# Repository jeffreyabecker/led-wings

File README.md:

# Wings

One-off LED-lit wing costume — off-the-shelf SK9822 strips cut into per-feather chunks, data
daisy-chained chunk-to-chunk, power fed from buck-module power-hubs, driven by a Pixelblaze.

## Build strategy

- **Off-the-shelf electrical system** — no custom PCBs for this build. SK9822 96 LED/m strips
  cut to per-feather LED counts; Pixelblaze V3 controller; buck-module + fuse power-hubs.
- Custom boards (KiCad 10 + `pcbnew` parameterized feathers) are deferred to "if we build
  more than one".

## Boards

- [Boards](boards/README.md) — the build plan: strip-chunk cut table, covert rows, controller,
  power hubs, settled COTS parts. **Source of truth for the electrical build.**

## Feather templates

- [Templates](mechanical/templates/) — **physical feather templating only**: outlines + geometry,
  the generator, and shape sourcing. No electronics content — lighting lives in
  [boards/lighting-and-boards.md](boards/lighting-and-boards.md).

## Mechanical

- [Mechanical](mechanical/) — physical wing structure: [structural](mechanical/structural/) frame

## Shared docs

- [Connector pinout](docs/connector-pinout.md) — pigtail wiring legend (PWR / DATA-IN / DATA-OUT wire pairs + colors)

## Investigations

- [Battery](investigations/battery/) — 12 V chemistry + sizing for 8 h @ 20 % mobility
- [Connectors](investigations/connectors/) — board-to-wire family options for the strip ends
  (pitch-split power/data, JLCPCB-assembled)

## Repository layout

- `boards/` — **electrical build**: strategy, feather lighting map, wiring legend, settled
  parts. All electronics information lives here (or in `docs/`).
- `mechanical/templates/` — **physical feather templating only**: outlines, geometry, generator,
  shape sourcing. No electronics/lighting content — that belongs in `boards/`.
- `mechanical/` — wing structure (frame, backplate, harness mounts).
- `docs/` — shared electrical references (connector pinout, pigtail crimp guide).
- `investigations/` — one-off research (battery, connectors, diffuser halo).

## Changing the plan

Update [boards/README.md](boards/README.md) — it is the single source of truth for the
electrical build.

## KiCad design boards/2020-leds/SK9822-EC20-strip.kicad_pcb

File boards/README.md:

# Boards — Off-the-Shelf Build Plan (one-off)

> ⚠️ **Board subset (2026-08, updated):** this build now makes **8 custom group boards/wing**
> (P, S, A, PC, SC, MC, L, U — [feather-boards.md](feather-boards.md)) + **4 × 6 A hub
> boards/wing** ([hub-board.md](hub-board.md)). The off-the-shelf strip-chunk plan below is
> **superseded for the boards** (retained as the parts/wiring reference and fallback).
>
> **Strategy (settled ✅):** this is a **one-off build** — the electrical system is assembled
> from off-the-shelf SK9822 strips and modules. **No custom PCBs for this build**; the
> parameterized custom-board plan (KiCad + `pcbnew`) and the 6-pin hub-routed idea are
> **deferred** to "if we ever build more than one".
>
> Status: ✅ settled · ⚠️ to confirm · ⬜ TBD.

| Role | Status | Implementation |
|------|--------|----------------|
| Feather lighting | ✅ | SK9822 strip chunks (96 LED/m), one cut per lit feather |
| Covert strip rows | ✅ | Continuous SK9822 strip spans, one cut per row |
| Controller | ✅ | Pixelblaze V3 + 74AHCT125 level shifter (COTS modules) |
| Power hub | ✅ | Buck modules + fuse blocks on perfboard |

## System (locked)

- **Split power/data.** Data daisy-chains feather→feather (pigtails) from one central
  Pixelblaze driving **both wings**; power fans out from hub clusters on a 12 V bus. 5 V
  exists only on the short hub→feather runs.
- **Controller:** Pixelblaze V3 Standard (ElectroMage) — ESP32, 8 data channels, 3.3 V logic.
  **Segmentation (settled ✅): N = 2 chains — one per wing** (all feathers + covert rows of
  that wing). No Output Expander.
- **Pixels:** ~1270 LEDs total both wings (see
  [feather lighting](lighting-and-boards.md)). Chain budget ≈ 635
  LEDs/channel on 2 channels — a full frame at 8 MHz SPI ≈ 2.5 ms, well inside any pattern
  frame rate.
- **Routing:** the two chains (one per wing) run along the wing's **top edge** (the feather
  bases — the only cable entrance); hubs sit along the same edge feeding short 5 V runs into
  clusters.

## LED medium — SK9822 strip

- **Strip (96/m only, settled ✅):** SK9822 **96 LED/m** (≈10.4 mm pitch), **10 mm wide**,
  5050 — the near-exact match to the 10 mm-pitch map. ⚠️ Vendor shortlist (96/m only):
  [Alibaba multi-density listing](https://www.alibaba.com/product-detail/Individually-Addressable-APA102-SK9822-30-60_1601370513576.html)
  (96/m option) or [JAD-LEDS 96/m](https://jad-leds.com/dc5v-ic-external-led-strip/467.html) —
  see settled parts; validate one reel before ordering the rest.
- **Feather = cut chunk.** One chunk per lit feather, cut per-LED (every LED carries its own
  chip). LED count = exposed-tip map + 2-LED bleed, at 10.4 mm pitch — same counts as the
  10 mm-pitch map:

  > ⚠️ Chunk lengths/LED counts below derive from **provisional** feather sizing — the
  > authoritative sizing lives in [`mechanical/templates/`](../mechanical/templates/),
  > **not yet finalized**; re-cut counts once it is locked.

  | Group | Exposed (cm) | Bleed | Chunk LEDs | Chunk length |
  |-------|-------------:|------:|-----------:|-------------:|
  | Primaries P1–P10 | 15 | +2 | 17 | ~17.7 cm |
  | Secondaries S1–S12 | 12 | +2 | 14 | ~14.6 cm |
  | Tertials T1–T4 | 10 | +2 | 12 | ~12.5 cm |
  | Greater coverts GC1–GC12 | 8 | +2 | 10 | ~10.4 cm |
  | Alula A-B/A-T | ~8 ⚠️ | +2 | ~10 ⚠️ | ~10.4 cm |

- **Chunk termination (settled ✅):** 6 stub wires soldered per chunk — `+5V`/`GND` (power,
  from a hub), `DI`/`CI` (data in), `DO`/`CO` (data out to the next feather) — then
  **2-pin JST-PNI crimped pigtails** (2.0 mm, wire-to-wire — both ends crimped, no headers):
  a receptacle `PNIRR-02VF` on each of power-in / data-in / data-out; all jumpers and feeds
  are plugs `PNIRP-02V-S` (data jumpers plug–plug, hub/controller feeds plug + bare wire).
  Wire pairs + colors are the [wiring legend](../docs/connector-pinout.md); parts + crimp
  procedure in [pigtail crimping](../docs/pigtail-crimping.md). Epoxy/glue strain relief over
  every pad set; bench-test each chunk before mounting (a bad joint darkens the whole
  downstream chain).
- **Covered base:** no strip at all — only the exposed tip + bleed is lit, so there are no
  hidden LEDs (and no idle-current waste).
- **Limits:** a 17-LED chunk ≈ 0.68 A full white — strip copper handles it easily; wiring
  planned so no single run exceeds ~2–3 A (PNI class rating).

## Covert strip rows

- One **continuous strip span per row** (median / lesser / marginal) — no cuts except row
  length, one common LED orientation by construction. The scallop silhouette lives in the
  overlay/diffuser, **not** in the strip.
- **Wiring per row:** `PWR` + `DI`/`CI` at the row head; `DO`/`CO` at the tail → next row's
  head (or its own chain).
- **Rows (working ⚠️):** median ~28 cm (~27 LEDs), lesser ×2 ~28 cm, marginal ~28 cm.
  Full-white per row ≈ 1.1 A — feed at the row head; mid-span power injection only if the
  bench shows drop.

## Controller — Pixelblaze (COTS)

- **Pixelblaze V3 Standard** (ElectroMage) — ✅ settled. 8 channels, 3.3 V logic, web UI
  live-coding (patterns ride for free). **N = 2 chains (settled ✅) — one per wing; no
  Output Expander.**
- **Level shifting:** the Pixelblaze's 3.3 V outputs need 5 V logic per chain — a
  74AHCT125-class shifter module (2 of 4 gates used) at the controller.
- Series R (33–100 Ω) at each chain head only if bench testing shows ringing; ESD/TVS
  optional for a one-off.

## Power hubs — modules, not boards

- **Buck:** **MP1584EN** module per cluster — rated 3 A, **practical ~2–2.5 A** at 12→5 V
  (**no heatsink needed**; ⚠️ buy from a reputable vendor — counterfeits common; bench-test
  each before install). One hub serves a feather cluster: ~0.4 A/feather full white,
  ~0.08 A @ 20 %. **Cluster sizing rule:** keep each hub ≤ ~2 A full-white (≈5 feathers), so
  it stays inside the no-heatsink envelope.
- **Protection:** fuse per 5 V feed (ATO inline holder or polyfuse), reverse-polarity MDD
  `SS34` ([C8678](https://www.lcsc.com/product-detail/C8678.html)) on the 12 V input.
- **Form:** perfboard — buck module + fuses + **push-in (spring-clamp) terminals**
  (Wago 2060-class) on the perfboard — **no screw terminals** (vibration-proof, tool-less,
  lower profile). **No data** on the hub.
- **Hub wiring:** 12 V bus → (fused + `SS34`) → push-in terminal → MP1584EN `IN+/IN−`;
  `OUT+/OUT−` → push-in 5 V terminals → PNI plug feeds to the chunks.
- **12 V bus:** daisy-chain hub-to-hub with **Wago 221 lever nuts** (tool-less splices,
  vibration-proof); drop-tolerant.
- **Why 12 V (settled):** a 5 V bus can't scale — on a 2 m / 12 AWG reference bus, full-white
  drops ~33 % (color shift; blue dies first) vs ~6 % on 12 V (~1 % @ 20 % brightness). One
  MP1584EN covers a hub's cluster at ≤ ~2 A full-white (~0.4 A @ 20 %) — inside its
  no-heatsink envelope.

## Settled parts (COTS)

| Item | Choice | Qty | Status | Source |
|------|--------|-----|--------|--------|
| LED strip | SK9822 96 LED/m, 10 mm wide, 5050 | ~15 m (3×5 m reels) | ⚠️ | [Alibaba 30/60/96/144 listing](https://www.alibaba.com/product-detail/Individually-Addressable-APA102-SK9822-30-60_1601370513576.html) · [JAD-LEDS 96/m](https://jad-leds.com/dc5v-ic-external-led-strip/467.html) |
| Controller | Pixelblaze V3 Standard | 1 | ✅ | [Tindie](https://www.tindie.com/products/electromage/pixelblaze-v3-standard-wifi-led-controller/) |
| Level shifter | Adafruit 74AHCT125 Quad Level-Shifter breakout (2 of 4 gates) | 1 | ✅ | [Adafruit 1787](https://www.adafruit.com/product/1787) |
| Buck | MP1584EN module (3 A; practical ~2–2.5 A, no heatsink) — cluster ≤ ~2 A full-white | ~6–8 | ⚠️ | [Amazon MP1584EN 5-pk](https://www.amazon.co.uk/DollaTek-MP1584EN-Step-Down-Adjustable-Converter/dp/B07DJ5HZ7G) — test each (counterfeits common) |
| Fuse | ATO inline holder per 5 V feed (alt. polyfuse e.g. Littelfuse 30R) | ~10 | ⚠️ | [Youngneer ATO kit](https://www.amazon.sg/Youngneer-Holders-Standard-Harness-Waterproof/dp/B07YY6KWSY) |
| Reverse polarity | MDD `SS34`, 3A 40V SMA | 1/hub | ✅ | [LCSC C8678](https://www.lcsc.com/product-detail/C8678.html) |
| PNI receptacle (chunk ends) | JST `PNIRR-02VF`, 2-pin | ~300 | ⬜ | TBD |
| PNI plug (jumpers/feeds) | JST `PNIRP-02V-S`, 2-pin | ~300 | ⬜ | TBD |
| PNI contacts | Socket `SPNI-001T-P0.5` + pin `BPNI-001T-P0.5` | ~650 + ~650 | ⬜ | TBD |
| Crimp tool | JST PN-family tool / ratchet + PN dies (SN-28B does NOT fit) | 1 | ⬜ | TBD |
| Wire | Silicone — 20–22 AWG red/black (power), 24 AWG data colors | ~15 m each | ⬜ | TBD |

## Open decisions (compact)

- Strip vendor: pick between the [Alibaba multi-density listing](https://www.alibaba.com/product-detail/Individually-Addressable-APA102-SK9822-30-60_1601370513576.html)
  and [JAD-LEDS](https://jad-leds.com/dc5v-ic-external-led-strip/467.html); confirm 10 mm
  width + open (non-waterproof) PCB, validate one reel before bulk
- Diffuser gap validation on 5050 emitters (prototype with the first reel)
- Buck module brand + bench test; fuse rating per feed
- Alula chunk size (confirm mockup); covert row spans once the layout is drawn

## Deferred (if we ever build more than one)

- Custom feather boards — 2020 SK9822 (`SK9822-EC20`, C2909059), JST connectors,
  parameterized KiCad 10 + `pcbnew` geometry (10 mm width, length + bend points).
- Custom power-hub PCB and controller carrier.
- Shelved idea: single 6-pin power+data connector per feather with hub-routed data chaining.

## References

- [Connector pinout / wiring legend](../docs/connector-pinout.md) — PWR / DATA-IN / DATA-OUT wire pairs + colors
- [Pigtail crimping](../docs/pigtail-crimping.md) — JST-PNI parts, counts, crimp procedure
- [Parts list](parts-list.md) — summarized COTS parts + potential vendors (battery excluded)
- [Battery](../investigations/battery/) — 12 V source sizing
- [Feather lighting](lighting-and-boards.md) — LED map + chunk counts
- [SK9822 datasheet (Normand LED)](http://www.normandled.com/upload/202003/SK9822-EC20%20LED%20Datasheet.pdf)

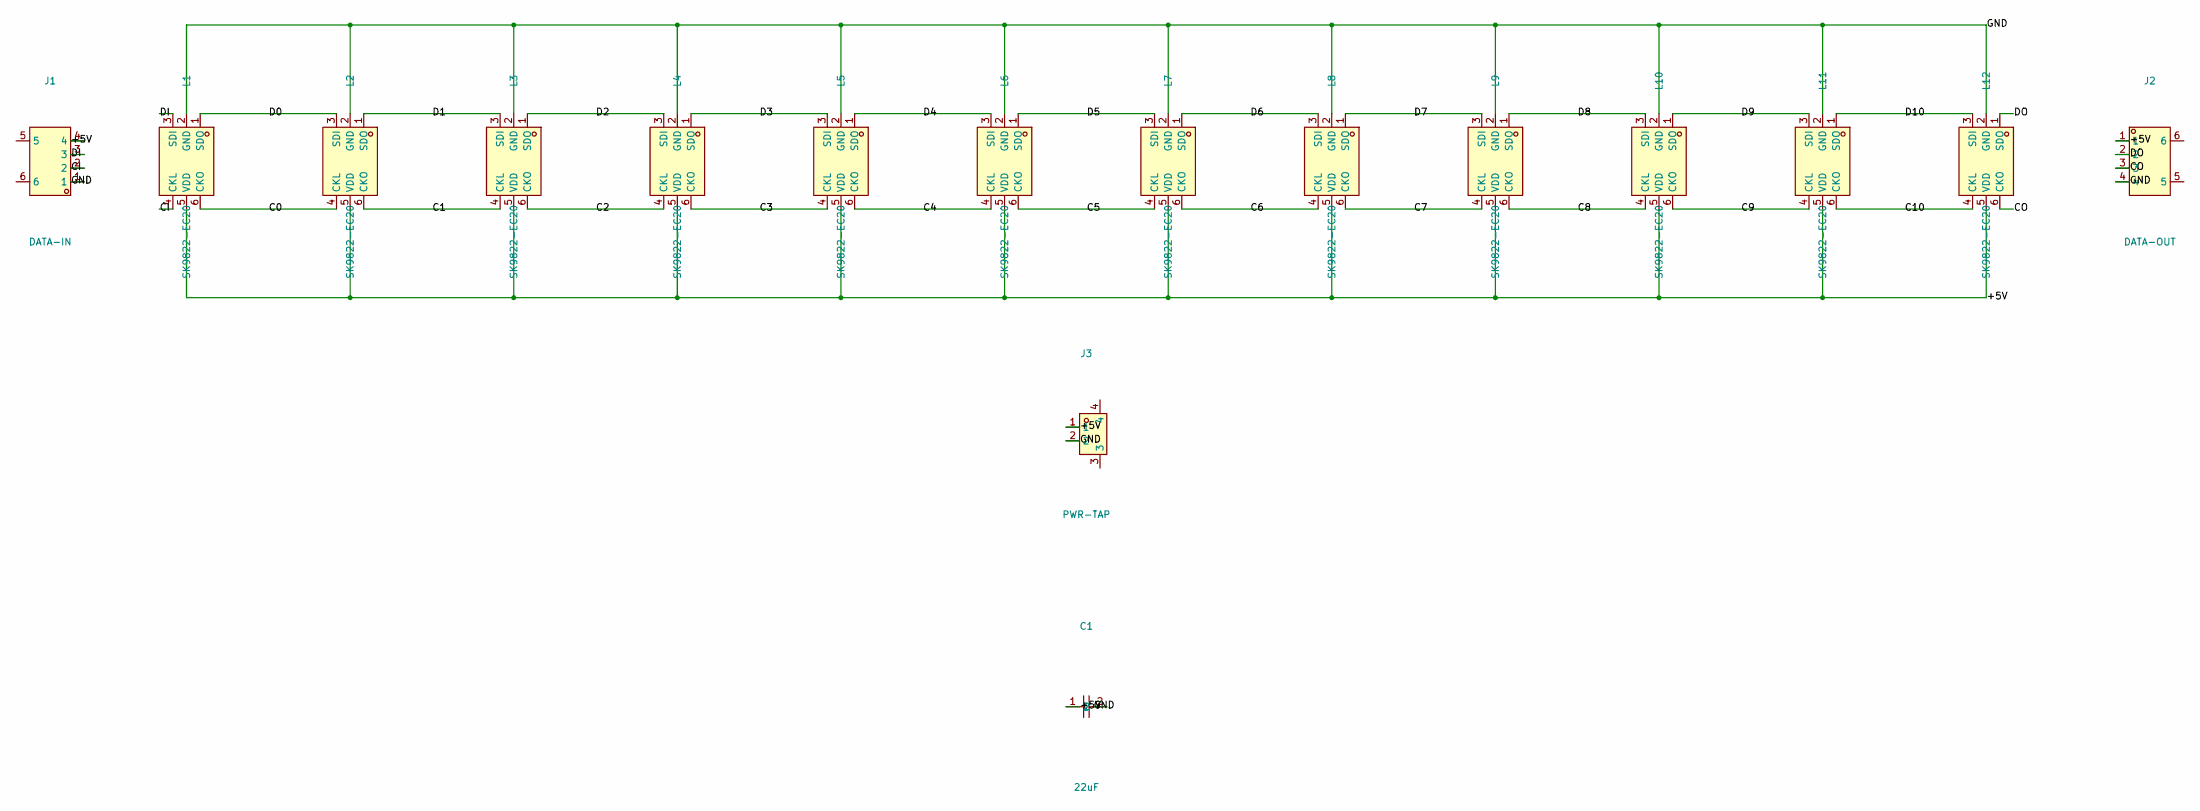
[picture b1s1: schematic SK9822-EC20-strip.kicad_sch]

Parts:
C1: 22uF; C1206
J1: DATA-IN; CONN-SMD_ZH1.5-4P_SMD
J2: DATA-OUT; CONN-SMD_ZH1.5-4P_SMD
J3: PWR-TAP; CONN-SMD_2P-P2.00_PH2.0-SPWB
L1, L2, L3, L4, L5, L6, L7, L8, L9, L10, L11, L12: SK9822-EC20; LED-SMD_6P-L2.0-W2.0-P0.80-TL

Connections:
/+5V: C1.1, J1.4, J2.1, J3.1, L1.5 (VDD), L2.5 (VDD), L3.5 (VDD), L4.5 (VDD), L5.5 (VDD), L6.5 (VDD), L7.5 (VDD), L8.5 (VDD), L9.5 (VDD), L10.5 (VDD), L11.5 (VDD), L12.5 (VDD)
/C0: L1.6 (CKO), L2.4 (CKL)
/C1: L2.6 (CKO), L3.4 (CKL)
/C2: L3.6 (CKO), L4.4 (CKL)
/C3: L4.6 (CKO), L5.4 (CKL)
/C4: L5.6 (CKO), L6.4 (CKL)
/C5: L6.6 (CKO), L7.4 (CKL)
/C6: L7.6 (CKO), L8.4 (CKL)
/C7: L8.6 (CKO), L9.4 (CKL)
/C8: L9.6 (CKO), L10.4 (CKL)
/C9: L10.6 (CKO), L11.4 (CKL)
/C10: L11.6 (CKO), L12.4 (CKL)
/CI: J1.2, L1.4 (CKL)
/CO: J2.3, L12.6 (CKO)
/D0: L1.1 (SDO), L2.3 (SDI)
/D1: L2.1 (SDO), L3.3 (SDI)
/D2: L3.1 (SDO), L4.3 (SDI)
/D3: L4.1 (SDO), L5.3 (SDI)
/D4: L5.1 (SDO), L6.3 (SDI)
/D5: L6.1 (SDO), L7.3 (SDI)
/D6: L7.1 (SDO), L8.3 (SDI)
/D7: L8.1 (SDO), L9.3 (SDI)
/D8: L9.1 (SDO), L10.3 (SDI)
/D9: L10.1 (SDO), L11.3 (SDI)
/D10: L11.1 (SDO), L12.3 (SDI)
/DI: J1.3, L1.3 (SDI)
/DO: J2.2, L12.1 (SDO)
/GND: C1.2, J1.1, J2.4, J3.2, L1.2 (GND), L2.2 (GND), L3.2 (GND), L4.2 (GND), L5.2 (GND), L6.2 (GND), L7.2 (GND), L8.2 (GND), L9.2 (GND), L10.2 (GND), L11.2 (GND), L12.2 (GND)

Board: 2 copper layers, 16 parts (0 on the bottom side), 28 nets, no tracks yet.
